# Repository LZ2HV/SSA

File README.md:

Start-Stop memory Module for MQB platforms as VW: T-CROSS, T-ROC, Polo, Taigo.<br/>
 With: PIC16F684 or PIC16F676 or PIC12F683 or PIC12F675, from Microchip and similar. 
 
Requirements to compile and understanding:
1. Compilator, CCS PCWHD v5.115.
2. SCH, Autodesk EAGLE v9.6.1.
3. Simulator for testing, Proteus Professional v8.13.
4. For writing into PIC, PICkit2 or PICkit3.<br/>
For PIC16F684 HEX is "mssa_pic16f684.hex", for PIC12F683 HEX is "mssa_pic12f683.hex",<br/>
for PIC16F676 HEX is "mssa_pic16f676.hex", for PIC12F675 HEX is "mssa_pic12f675.hex".

Connections: For T-Cross (Switch module 1 in centre console, module EX23, 10 pins connector black),
1. LED = PWM signal 200Hz duty cycle 5-90%, and or DC (12V) signal, from Start/Stop LED, (pin 6).
2. BUT = Button Start/Stop (pin 3).
3. 12V = KL15, ignition (pin 9).
4. GND = GND (pin 1).

How its work:
1. If Start/Stop System is switched to off from ((A) car button), this state will be saved after 1sec.
2. If Start/Stop System is switched to on from ((A) car button), this state will be saved after 4sec.
3. At start ignition saved (Start/Stop System is off) will be returned after 6sec (6sec is default value).
4. If you wanna to change this 6sec, just push once button in the module, module LED, will be flashing 7 times = 7sec,
next bush of the button, will be change to 8sec, module LED, will be flashing 8 times ... (2 to 8sec).
5. Main cicle of the device is indicated from module LED, every 3sec one short flashing.

Schematics and boards is in directory "sch", thers have three variants, two with DIP socket one with SMD elements,
 in down pictures is presented variant with SMD elements (directory sch/smd). 
 
<strong>Important: If you are not tech savvy, do not attempt this.</strong><br/><br/>
<strong>An important part of the circuits is the PWM and DC detector shown in the picture below.</strong><br/>.
<br/>

<strong>SMD variant: Gerber file sch/smd/mssaPIC12smd_2026-07-19.zip</strong>
1. All zero resistors are not placed at the beginning (R9, R13, R14).
2. Resistor R9 are placed after successfully programming.  
3. If Button Start-Stop work with GND (T-Cross) Add R14, Remove R10 and R13.
4. If Button Start-Stop work with Plus (some Skoda models) Add R13, Remove R14.<br/>

<br/>

<strong>DIP PIC12 variant: Gerber file sch/mssaPIC12_2026-07-19.zip, This variant work only for Button with GND.</strong><br/>

<br/>

<strong>DIP PIC16 variant: Gerber file sch/mssaPIC16_2026-07-19.zip, This variant work only for Button with GND.</strong><br/>

<br/>

<strong>First prototype with pic16: In My VW T-Cross 2025</strong><br/>
<br/>
<strong>Second prototype with pic12:</strong><br/>

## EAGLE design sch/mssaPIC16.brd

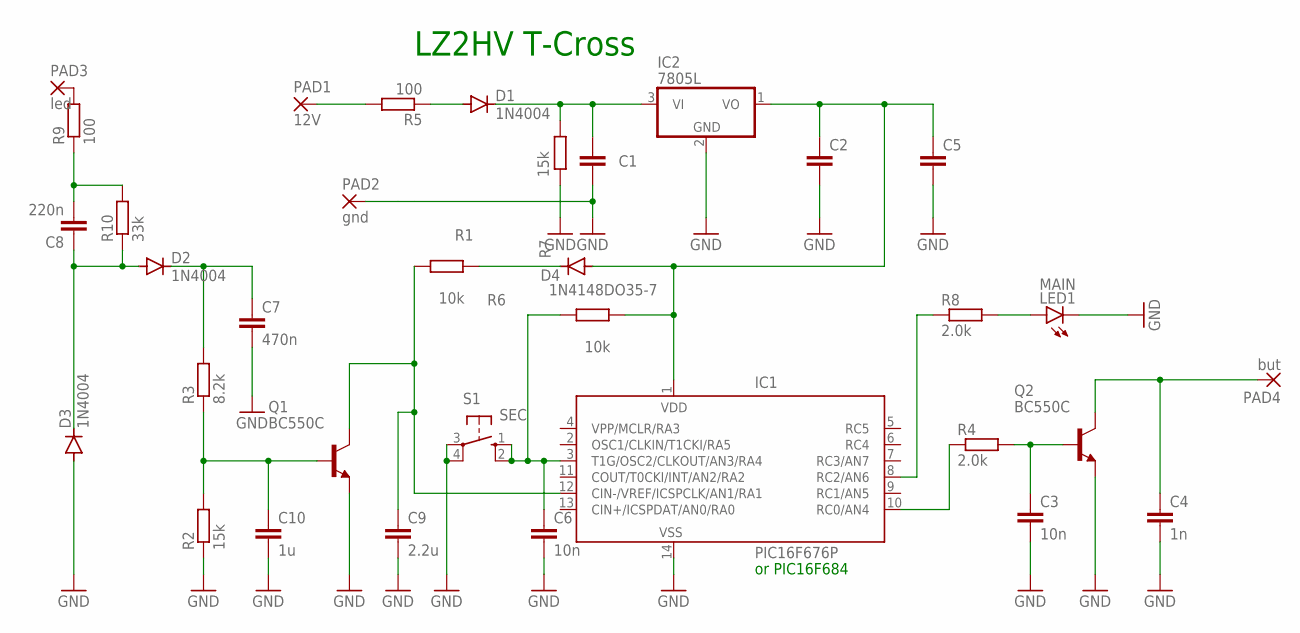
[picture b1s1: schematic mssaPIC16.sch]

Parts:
C1: 100n; C5B2.5
C2: 101n; C5B2.5
C3, C6: 10n; C5B2.5
C4: 1n; C5B2.5
C5, C8: 220n; C5B2.5
C7: 470n; C5B2.5
C9: 2.2u; C5B2.5
C10: 1u; C5B2.5
D1, D2, D3: 1N4004; DO41-10
D4: 1N4148DO35-7; DO35-7
IC1: PIC16F676P; DIL14
IC2: 7805L; TO92
LED1: MAIN; LED3MM
PAD1: 12V; 2,54/1,0
PAD2: gnd; 2,54/1,0
PAD3: led; 2,54/1,0
PAD4: but; 2,54/1,0
Q1, Q2: BC550C; TO92-EBC
R1, R6: 10k; 0207/7
R2, R7: 15k; 0207/7
R3: 8.2k; 0207/7
R4, R8: 2.0k; 0207/7
R5: 100; 0207/7
R9: 100; 0207/2V
R10: 33k; 0207/2V
S1: SEC; B3F-10XX

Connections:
GND: C1.2, C2.2, C3.2, C4.2, C5.2, C6.2, C7.2, C9.2, C10.2, D3.A, IC1.14 (VSS), IC2.2 (GND), LED1.K (C), PAD2.1, Q1.E, Q2.E, R2.1, R7.1, S1.3, S1.4 (P1)
unnamed: C1.1, D1.C, IC2.3 (VI), R7.2
unnamed: C2.1, C5.1, D4.A, IC1.1 (VDD), IC2.1 (VO), R6.2
unnamed: C10.1, Q1.B, R2.2, R3.1
unnamed: C9.1, IC1.12 (CIN-/VREF/ICSPCLK/AN1/RA1), Q1.C, R1.1
unnamed: PAD1.1, R5.2
unnamed: IC1.10 (RC0/AN4), R4.1
unnamed: C3.1, Q2.B, R4.2
unnamed: C4.1, PAD4.1, Q2.C
unnamed: C7.1, D2.C, R3.2
unnamed: D1.A, R5.1
unnamed: C6.1, IC1.3 (T1G/OSC2/CLKOUT/AN3/RA4), R6.1, S1.1 (S), S1.2 (S1)
unnamed: C8.2, R9.1, R10.2
unnamed: C8.1, D2.A, D3.C, R10.1
unnamed: LED1.A, R8.2
unnamed: IC1.8 (RC2/AN6), R8.1
unnamed: D4.C, R1.2
unnamed: PAD3.1, R9.2

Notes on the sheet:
LZ2HV T-Cross
or PIC16F684

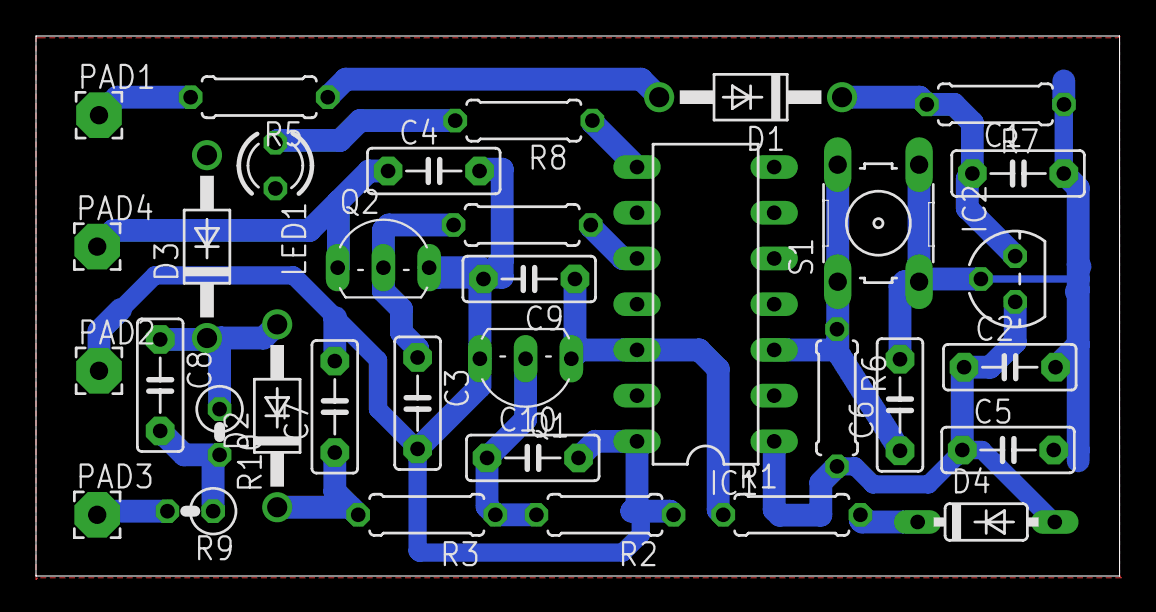
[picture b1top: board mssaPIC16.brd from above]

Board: 2 copper layers, 60.2 x 30.0 mm, 34 parts (0 on the bottom side), 18 nets.

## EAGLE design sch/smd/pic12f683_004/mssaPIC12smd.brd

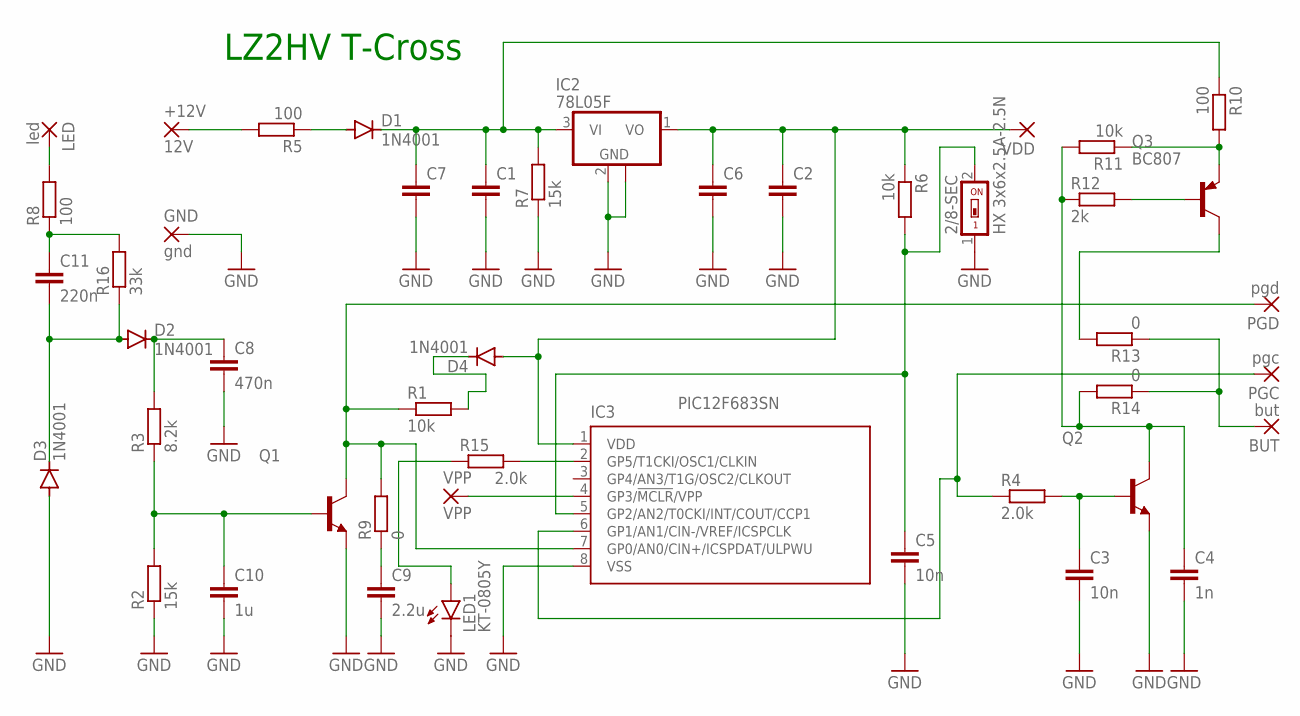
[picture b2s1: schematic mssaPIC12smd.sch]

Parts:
2/8-SEC: HX 3x6x2.5A-2.5N; SMS-001
+12V: 12V; 3,17/1,3
BUT: but; 3,17/1,3
C1, C6, C7: 100n; C1206K
C2, C11: 220n; C1206K
C3, C5: 10n; C1206K
C4: 1n; C1206K
C8: 470n; C1206K
C9: 2.2u; C1206K
C10: 1u; C1206K
D1, D2, D3, D4: 1N4001; SOD-123_MINI-SMA
GND: gnd; 3,17/1,3
IC2: 78L05F; SOT89
IC3: PIC12F683SN; SO-08
LED: led; 3,17/1,3
LED1: KT-0805Y; CHIP-LED0805
PGC: pgc; 2,15/1,0
PGD: pgd; 2,15/1,0
Q1, Q2: BC817; SOT23-BEC
Q3: BC807; SOT23-BEC
R1, R6, R11: 10k; M1206
R2, R7: 15k; M1206
R3: 8.2k; M1206
R4: 2.0k; M1206
R5, R8, R10: 100; M1206
R9, R13, R14: 0; R0603
R12: 2k; M1206
R15: 2.0k; R0603
R16: 33k; M1206
VDD: VDD; 2,15/1,0
VPP: VPP; 2,15/1,0

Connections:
GND: 2/8-SEC.1, C1.2, C2.2, C3.2, C4.2, C5.2, C6.2, C7.2, C8.2, C9.2, C10.2, D3.A, GND.1, IC2.2 (GND), IC2.2@1 (GND), IC3.8 (VSS), LED1.C, Q1.E, Q2.E, R2.1, R7.1
unnamed: C1.1, C7.1, D1.C, IC2.3 (VI), R7.2, R10.1
unnamed: C11.2, D2.A, D3.C, R16.1
unnamed: C10.1, Q1.B, R2.2, R3.1
unnamed: IC3.7 (GP0/AN0/CIN+/ICSPDAT/ULPWU), PGD.1, Q1.C, R1.1, R9.2
unnamed: +12V.1, R5.2
unnamed: IC3.6 (GP1/AN1/CIN-/VREF/ICSPCLK), PGC.1, R4.1
unnamed: C3.1, Q2.B, R4.2
unnamed: C4.1, Q2.C, R11.2, R12.1, R14.2
unnamed: C8.1, D2.C, R3.2
unnamed: D1.A, R5.1
unnamed: IC3.4 (GP3/!MCLR!/VPP), VPP.1
unnamed: 2/8-SEC.2, C5.1, IC3.5 (GP2/AN2/T0CKI/INT/COUT/CCP1), R6.2
unnamed: C11.1, R8.1, R16.2
unnamed: LED.1, R8.2
unnamed: C9.1, R9.1
unnamed: Q3.E, R10.2, R11.1
unnamed: Q3.C, R13.2
unnamed: Q3.B, R12.2
unnamed: BUT.1, R13.1, R14.1
unnamed: IC3.2 (GP5/T1CKI/OSC1/CLKIN), R15.2
unnamed: LED1.A, R15.1
unnamed: D4.C, R1.2
VDD: C2.1, C6.1, D4.A, IC2.1 (VO), IC3.1 (VDD), R6.1, VDD.1

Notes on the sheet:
LZ2HV T-Cross

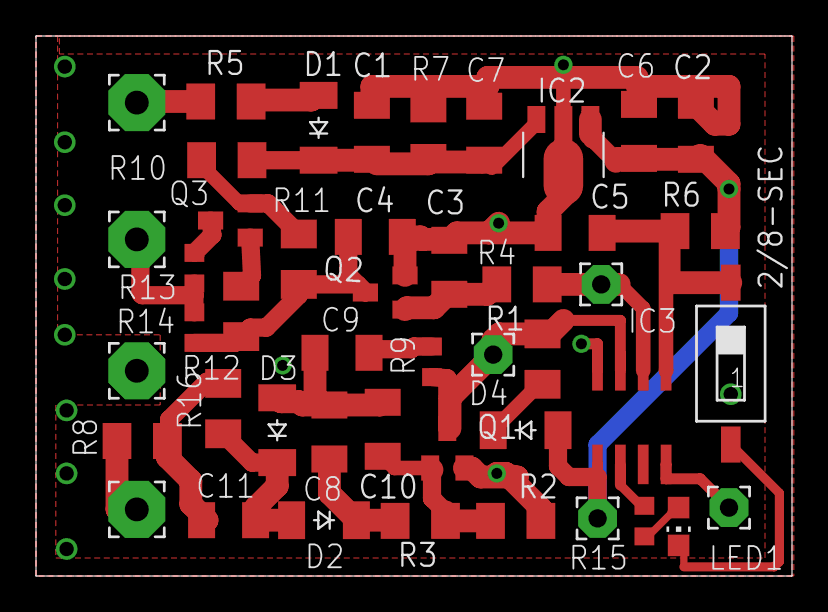
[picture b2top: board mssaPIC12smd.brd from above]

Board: 2 copper layers, 42.0 x 30.0 mm, 46 parts (0 on the bottom side), 24 nets.

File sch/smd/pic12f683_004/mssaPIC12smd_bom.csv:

Comment,Designator,Footprint,LCSC Part #
0,R9 R13 R14,R0603,
1N4001,D1 D2 D3 D4,SOD-123_MINI-SMA,
1n,C4,C1206K,
1u,C10,C1206K,
2.0k,R4,M1206,
2.0k,R15,R0603,
2.2u,C9,C1206K,
2k,R12,M1206,
8.2k,R3,M1206,
10k,R1 R6 R11,M1206,
10n,C3 C5,C1206K,
12V,+12V,3 17/1 3,
15k,R2 R7,M1206,
33k,R16,M1206,
78L05F,IC2,SOT89,
100,R5 R8 R10,M1206,
100n,C1 C6 C7,C1206K,
220n,C2 C11,C1206K,
470n,C8,C1206K,
BC807,Q3,SOT23-BEC,
BC817,Q1 Q2,SOT23-BEC,
HX 3x6x2.5A-2.5N,2/8-SEC,SMS-001,
KT-0805Y,LED1,CHIP-LED0805,
PIC12F683SN,IC3,SO-08,
VDD,VDD,2 15/1 0,
VPP,VPP,2 15/1 0,
but,BUT,3 17/1 3,
gnd,GND,3 17/1 3,
led,LED,3 17/1 3,
pgc,PGC,2 15/1 0,
pgd,PGD,2 15/1 0,

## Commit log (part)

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2026-06-17 SSA v.024
2026-06-18 SSA v.026
2026-06-22 SSA v.027
2026-06-23 SSA v.030
2026-06-29 SSA v.032
2026-06-30 SSA v.033
